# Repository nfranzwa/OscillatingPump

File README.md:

UCSD MAE 156 Capstone Project

Link to UCSD Capstone Project Overview https://sites.google.com/eng.ucsd.edu/mae156b-2025winter-team06

The provided code was developed using Arduino IDE and the Platform.io extension on VS Code.
While it is possible to flash/deploy our software to an ESP32 through other means, we heavily recommend the two for ease of installing dependencies and following subsequent instructions.

# Setup
In order to flash the GPIO ESP or Web ESP, first make a local copy of the most recent version of this repository by clicking `<Code>` and either:

 - Copying and running the command in terminal (requires github cli installation or git)
 - Opening through Github Desktop (requires installing the Github Desktop app)
 - Downloading and extracting the code from a .zip file

The next steps assume you have a local copy of the provided code.

# Installing Libraries

## GPIO ESP

Click the Platform IO icon on the left edge of VS Code, then navigate to `Quick Access > PIO Home > Projects & Configuration`.

Select `Add Existing`.

Navigate to the directory `drive/path/to/repository/OscillatingPump/ESP32_CTRL` and select `Open "ESP32_CTRL`.

Shortly, Platform IO should be setting up the project according to the `platform.ini` file in the selected folder, most importantly installing libraries that are used in the project.

## Web ESP

Open the Arduino sketch named `webesp.ino` located in `/WebappCode/webesp/webesp/`.

Navigate to the library manager.

Search for and install the following libraries:
 - Arduino_JSON by Arduino
 - Async TCP by ESP32Async
 - ESP Async WebServer by ESP32ASync
 - EspSoftwareSerial by Dirk Kaar, Peter Lerup

In the top menu, Navigate to `Sketch > Include Library`, and include the following:
 - WiFi
 - LittleFS

The next step is to install ESP32 LittleFS uploader to the Arduino IDE.

Go to [[https://github.com/earlephilhower/arduino-littlefs-upload/releases]] and download the latest version of `arduino-littlefs-upload-x.x.x.vsix`.

Windows: 
1. In File Explorer, navigate to `C:\Users\<username>\.arduinoIDE\`
2. Create a folder called `plugins` if it doesn't already exist.
3. Move the downloaded `.vsix` file into this folder.

Mac OS: 
1. In Finder, navigate to `~/.arduinoIDE`
2. Create a new folder called `plugins`
3. Move the downloaded `.vsix` file into this folder.

Restart the Arduino IDE, and make sure the plug-in was successfully installed by opening the command palette with `Ctrl/Cmd + Shift + P` and ensuring `Upload LittleFS to Pico/ESP8266/ESP32` is an available command.

# Uploading/Deploying code to the ESP32's

With the environments and libraries set up, one can compile and deploy the code through the following procedures.

## GPIO ESP

On the bottom bar, ensure that the Platform IO project is ESP32_CTRL and you are deploying to the right COM port (leave as `Auto` unless multiple ESP's are connected to same computer).

The code will be compiled and deployed to the ESP32 when pressing the `→` button.
 - one can also compile the code without deploying by pressing the `✓` button.

A new terminal should open within VS Code, displaying compile messages. When the terminal says `Connecting...`
Press and hold the `Boot` button on the ESP until the terminal shows that code is being written to the ESP32.

## Web ESP
First, Go to `Sketch > Show Sketch Folder` and ensure that the `data/` folder from our repository is there. This contains files that are to be uploaded to the ESP32 filesystem.

Open the command palette and run `Upload LittleFS to Pico/ESP8266/ESP32`.

After getting a `Completed upload` message, compile and deploy the sketch to the ESP32 by pressing the `→` button.
 - one can also compile the code without deploying by pressing the `✓` button.

When the terminal says `Connecting...`
Press and hold the `Boot` button on the ESP until the terminal shows that code is being written to the ESP32.

# Troubleshooting code
If the ESP's are consistently not behaving as expected, we provide debugging statements through Serial Monitors, which can be accessed through the Command Palette of both VS Code and Arduino IDE.

Issues to check may include whether an ESP is:
 - constantly restarting (stuck in a boot loop)
 - unable to communicate through serial with the other ESP
 - some particular features are not behaving as expected
 - error codes being thrown by an ESP

The GPIO ESP has an ongoing task that reads the Serial port between the computer and ESP, providing the user with the following inputs and features:

| User Input      | Feature                                                            |
| --------------- | ------------------------------------------------------------------ |
| `debug`         | toggles debugging statements for Serial communication between ESPs |
| `cal debug`     | toggles debugging statements for during calibration                |
| `wave debug`    | toggles debugging statements for wave generation                   |
| `show pm`       | prints out the current pressure map vector                         |
| `m:#.## M:#.##` | manually overwrite the target min and max pressure                 |
| `c:#`           | manually overwrite the calibration state                           |

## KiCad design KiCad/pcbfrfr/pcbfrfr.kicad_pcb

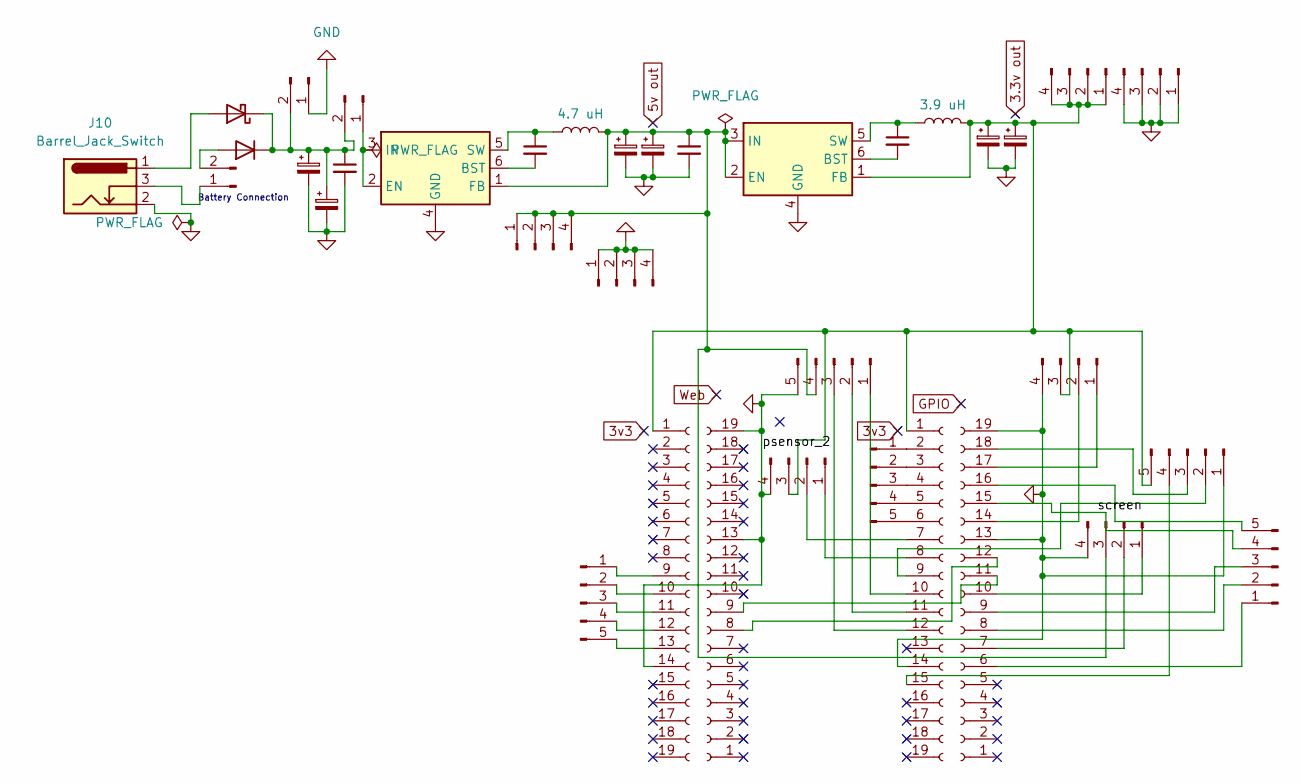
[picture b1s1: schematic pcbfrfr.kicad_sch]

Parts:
C1: 10 uF; CP_Radial_D4.0mm_P1.50mm
C2, C8: 100 nF; C_0402_1005Metric
C3, C4, C9, C10: 22 uF; C_0805_2012Metric
C5: 1000 uF; CP_Radial_D10.0mm_P5.00mm
C6, C7: 0.1 uF; C_0402_1005Metric
D2: US2AA; D_SMA
D3: SS24; D_SMA
J1, J11, J16, J17, J18: Conn_01x05_Pin; PinHeader_1x05_P2.54mm_Vertical
J2: battery; PinHeader_1x02_P2.54mm_Vertical
J3, J4, J5, J7: Conn_01x19_Socket; PinHeader_1x19_P2.54mm_Vertical
J6, J8, J9, J12, J13, J14, J15: Conn_01x04_Pin; PinHeader_1x04_P2.54mm_Vertical
J10: Barrel_Jack_Switch; BarrelJack_CLIFF_FC681465S_SMT_Horizontal
J21: mtr; PinHeader_1x02_P2.54mm_Vertical
J22: estop; PinHeader_1x02_P2.54mm_Vertical
L1: 4.7 uH; L_Changjiang_FXL0530
L3: 3.9 uH; L_Changjiang_FXL0530
U1: AP63203WU; TSOT-23-6
U2: AP63205WU; TSOT-23-6

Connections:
/screen: J5.15, J17.4
GND: C1.2, C3.2, C4.2, C5.2, C6.2, C7.2, C9.2, C10.2, J1.5, J3.14, J4.14, J5.13, J5.19, J6.4, J7.13, J7.19, J8.4, J9.4, J10.2, J11.1, J13.1, J13.2, J13.3, J13.4, J15.1, J15.2, J15.3, J15.4, J21.1, U1.4 (GND), U2.4 (GND)
unnamed: D2.2 (A), J2.2
unnamed: C1.1, C5.1, C6.1, D2.1 (K), D3.1 (K), J21.2, J22.2
unnamed: D3.2 (A), J10.1
unnamed: J1.1, J4.10
unnamed: J1.2, J4.11
unnamed: J1.3, J4.12
unnamed: C3.1, C4.1, C7.1, J1.4, J9.3, J12.1, J12.2, J12.3, J12.4, L1.2, U1.2 (EN), U1.3 (IN), U2.1 (FB)
unnamed: J2.1, J10.3
unnamed: J4.7, J8.2
unnamed: J4.8, J8.1
unnamed: J5.7, J9.2
unnamed: J5.10, J9.1
unnamed: J5.11, J7.9
unnamed: J5.12, J7.8
unnamed: J5.14, J6.2
unnamed: J5.17, J6.1
unnamed: J4.9, J11.2
unnamed: J5.18, J11.3
unnamed: J4.15, J11.4
unnamed: C9.1, C10.1, J3.1, J4.1, J6.3, J8.3, J11.5, J14.1, J14.2, J14.3, J14.4, L3.2, U1.1 (FB)
unnamed: J4.2, J16.1
unnamed: J4.3, J16.2
unnamed: J4.4, J16.3
unnamed: J4.5, J16.4
unnamed: J4.6, J16.5
unnamed: J5.6, J17.1
unnamed: J5.8, J17.2
unnamed: J5.9, J17.3
unnamed: J5.16, J17.5
unnamed: J3.9, J18.1
unnamed: J3.10, J18.2
unnamed: J3.11, J18.3
unnamed: J3.12, J18.4
unnamed: J3.13, J18.5
unnamed: J22.1, U2.2 (EN), U2.3 (IN)
unnamed: C8.2, U1.6 (BST)
unnamed: C8.1, L3.1, U1.5 (SW)
unnamed: C2.2, U2.6 (BST)
unnamed: C2.1, L1.1, U2.5 (SW)

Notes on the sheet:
Battery Connection

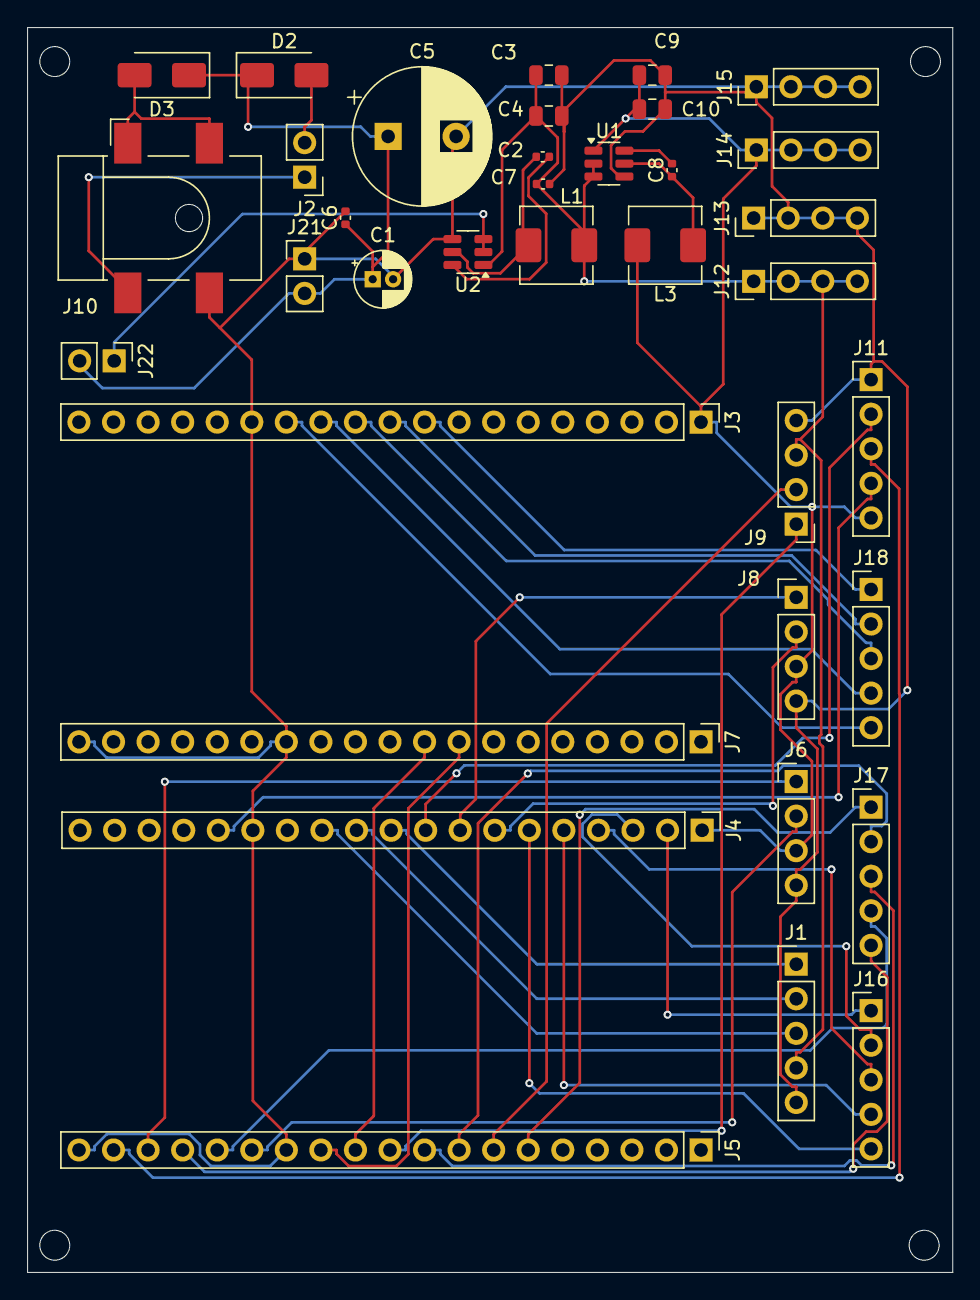
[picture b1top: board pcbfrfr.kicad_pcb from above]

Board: 2 copper layers, 68.0 x 91.5 mm, 36 parts (0 on the bottom side), 41 nets.

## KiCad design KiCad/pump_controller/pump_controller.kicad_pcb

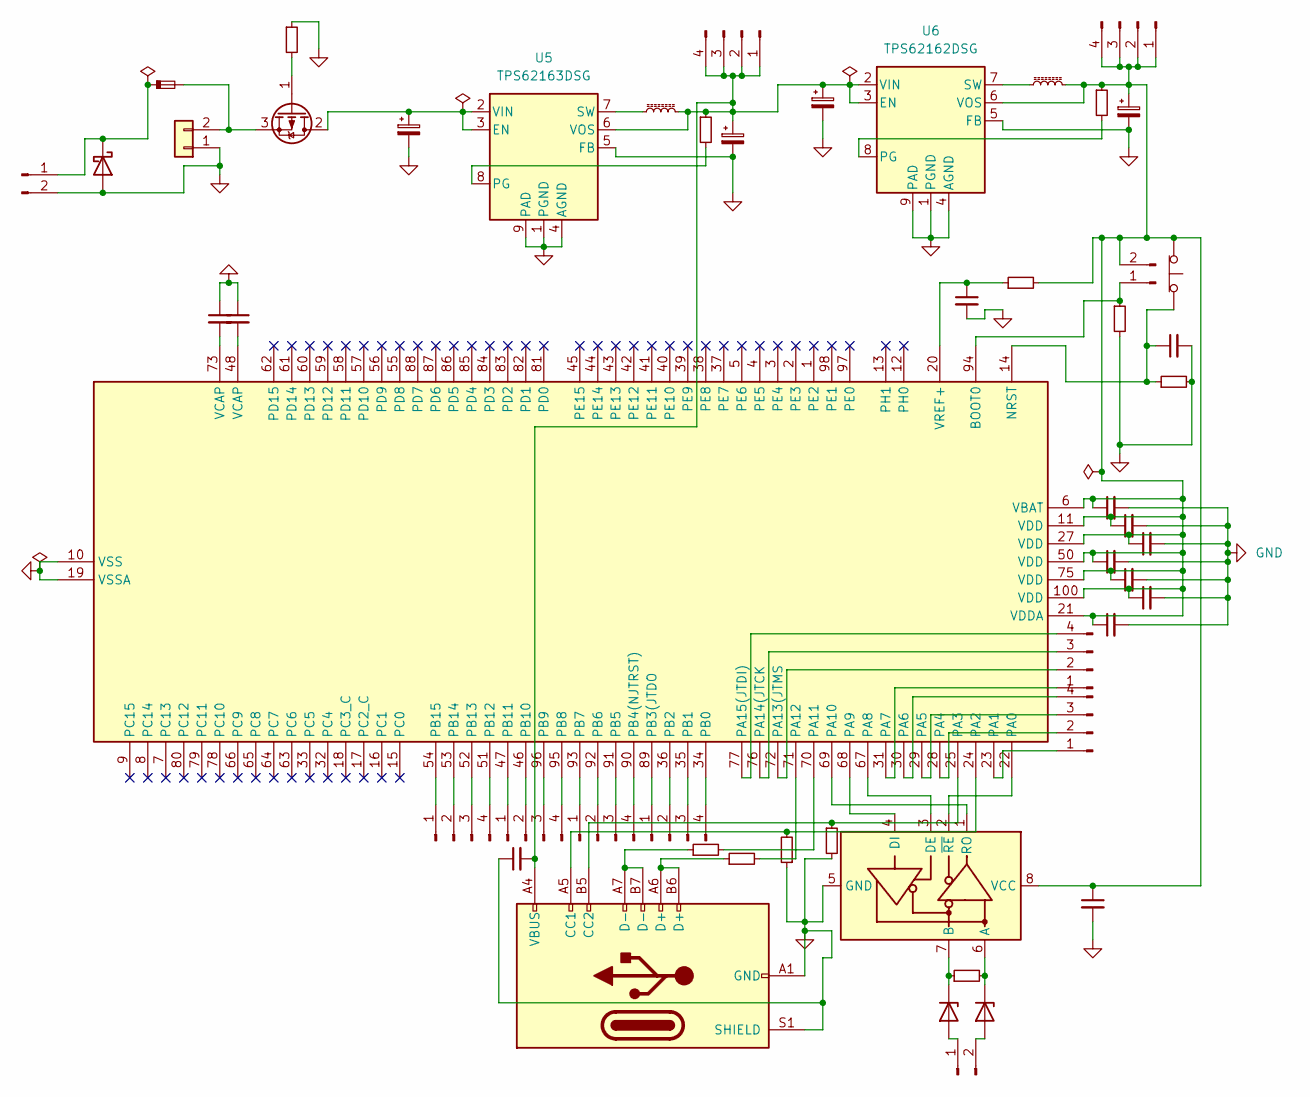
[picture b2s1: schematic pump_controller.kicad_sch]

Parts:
C2, C3: 2.2 uF; C_0402_1005Metric
C6, C10, C13, C14, C15, C16, C18, C19, C20, C21, C22: 0.1 uF; C_0402_1005Metric
C23, C25: 10 uF; CP_Elec_10x10.5
C24, C26: 22 uF; C_0805_2012Metric
D3, D5: PTVS7V5Z1USK; Nexperia_DSN1608-2_1.6x0.8mm
D6: 1N5819; D_DO-41_SOD81_P10.16mm_Horizontal
F2: 5A; Fuse_0805_2012Metric
J1, J2, J10, J12, J13, J17, J22, J23: Conn_01x04_Pin; PinHeader_1x04_P2.54mm_Vertical
J15: USB_C_Receptacle_USB2.0_14P; USB_C_Receptacle_HRO_TYPE-C-31-M-12
J21, J25, J30: Conn_01x02_Pin; PinHeader_1x02_P2.54mm_Vertical
J28: Conn_01x02; TerminalBlock_Phoenix_MKDS-1,5-2_1x02_P5.00mm_Horizontal
L3, L4: 2.2 uH; L_0805_2012Metric
Q2: IRF9540N; TO-220-3_Vertical
R2, R3, R7: 22; R_0402_1005Metric
R4, R5: 5100; R_0402_1005Metric
R6: 120; R_0402_1005Metric
R8, R9, R10: 10k; R_0402_1005Metric
R11, R12: 100k; R_0402_1005Metric
SW1: SW_Push_Open; SW_SPST_TL3342
U2: STM32H723VGTx; LQFP-100_14x14mm_P0.5mm
U4: MAX3075E; SOIC-8_3.9x4.9mm_P1.27mm
U5: TPS62163DSG; WSON-8-1EP_2x2mm_P0.5mm_EP0.9x1.6mm_ThermalVias
U6: TPS62162DSG; WSON-8-1EP_2x2mm_P0.5mm_EP0.9x1.6mm_ThermalVias

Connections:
GND: C2.1, C3.1, C6.1, C10.2, C13.2, C14.2, C15.2, C16.2, C18.2, C19.2, C20.2, C21.2, C22.2, C23.2, C24.2, C25.2, C26.2, D6.2 (A), J15.A1 (GND), J15.A12 (GND), J15.B1 (GND), J15.B12 (GND), J15.S1 (SHIELD), J28.1, J30.2, R4.1, R5.2, R8.2, R9.2, R10.1, U2.10 (VSS), U2.19 (VSSA), U2.26 (VSS), U2.49 (VSS), U2.74 (VSS), U2.99 (VSS), U4.5 (GND), U5.1 (PGND), U5.4 (AGND), U5.5 (FB), U5.9 (PAD), U6.1 (PGND), U6.4 (AGND), U6.5 (FB), U6.9 (PAD)
unnamed: C2.2, U2.73 (VCAP)
unnamed: C3.2, U2.48 (VCAP)
unnamed: D3.2 (A), J21.1
unnamed: D3.1 (K), R6.1, U4.7 (B)
unnamed: D5.2 (A), J21.2
unnamed: D5.1 (K), R6.2, U4.6 (A)
unnamed: D6.1 (K), F2.1, J30.1
unnamed: C6.2, C24.1, C25.1, J1.1, J1.2, J1.3, J1.4, J15.A4 (VBUS), J15.A9 (VBUS), J15.B4 (VBUS), J15.B9 (VBUS), L3.2, R11.1, U5.6 (VOS), U6.2 (VIN), U6.3 (EN)
unnamed: C13.1, C14.1, C15.1, C16.1, C18.1, C19.1, C20.1, C21.1, C26.1, J2.1, J2.2, J2.3, J2.4, J25.2, L4.2, R7.2, R12.1, SW1.1 (A), U2.6 (VBAT), U2.11 (VDD), U2.21 (VDDA), U2.27 (VDD), U2.50 (VDD), U2.75 (VDD), U2.100 (VDD), U4.8 (VCC), U6.6 (VOS)
unnamed: J10.1, U2.54 (PB15)
unnamed: J10.2, U2.53 (PB14)
unnamed: J10.3, U2.52 (PB13)
unnamed: J10.4, U2.51 (PB12)
unnamed: J12.1, U2.47 (PB11)
unnamed: J12.2, U2.46 (PB10)
unnamed: J12.3, U2.96 (PB9)
unnamed: J12.4, U2.95 (PB8)
unnamed: J13.1, U2.93 (PB7)
unnamed: J13.2, U2.92 (PB6)
unnamed: J13.3, U2.91 (PB5)
unnamed: J13.4, U2.90 (PB4(NJTRST))
unnamed: J15.A5 (CC1), R4.2, U2.24 (PA2)
unnamed: J15.B5 (CC2), R5.1, U2.25 (PA3)
unnamed: J15.A6 (D+), J15.B6 (D+), R3.1
unnamed: J15.A7 (D-), J15.B7 (D-), R2.1
unnamed: J17.1, U2.89 (PB3(JTDO)
unnamed: J17.2, U2.36 (PB2)
unnamed: J17.3, U2.35 (PB1)
unnamed: J17.4, U2.34 (PB0)
unnamed: J22.1, U2.31 (PA7)
unnamed: J22.2, U2.72 (PA13(JTMS)
unnamed: J22.3, U2.76 (PA14(JTCK)
unnamed: J22.4, U2.77 (PA15(JTDI))
unnamed: J23.1, U2.23 (PA1)
unnamed: J23.2, U2.28 (PA4)
unnamed: J23.3, U2.29 (PA5)
unnamed: J23.4, U2.30 (PA6)
unnamed: J25.1, R8.1, U2.94 (BOOT0)
unnamed: F2.2, J28.2, Q2.3 (S)
unnamed: C23.1, Q2.2 (D), U5.2 (VIN), U5.3 (EN)
unnamed: Q2.1 (G), R10.2
unnamed: C22.1, R9.1, SW1.2 (B), U2.14 (NRST)
unnamed: U2.22 (PA0), U4.2 (~RE)
unnamed: U2.67 (PA8), U4.3 (DE)
unnamed: U2.68 (PA9), U4.4 (DI)
unnamed: U2.69 (PA10), U4.1 (RO)
unnamed: R2.2, U2.70 (PA11)
unnamed: R3.2, U2.71 (PA12)
unnamed: C10.1, R7.1, U2.20 (VREF+)
unnamed: R11.2, U5.8 (PG)
unnamed: L3.1, U5.7 (SW)
unnamed: R12.2, U6.8 (PG)
unnamed: L4.1, U6.7 (SW)

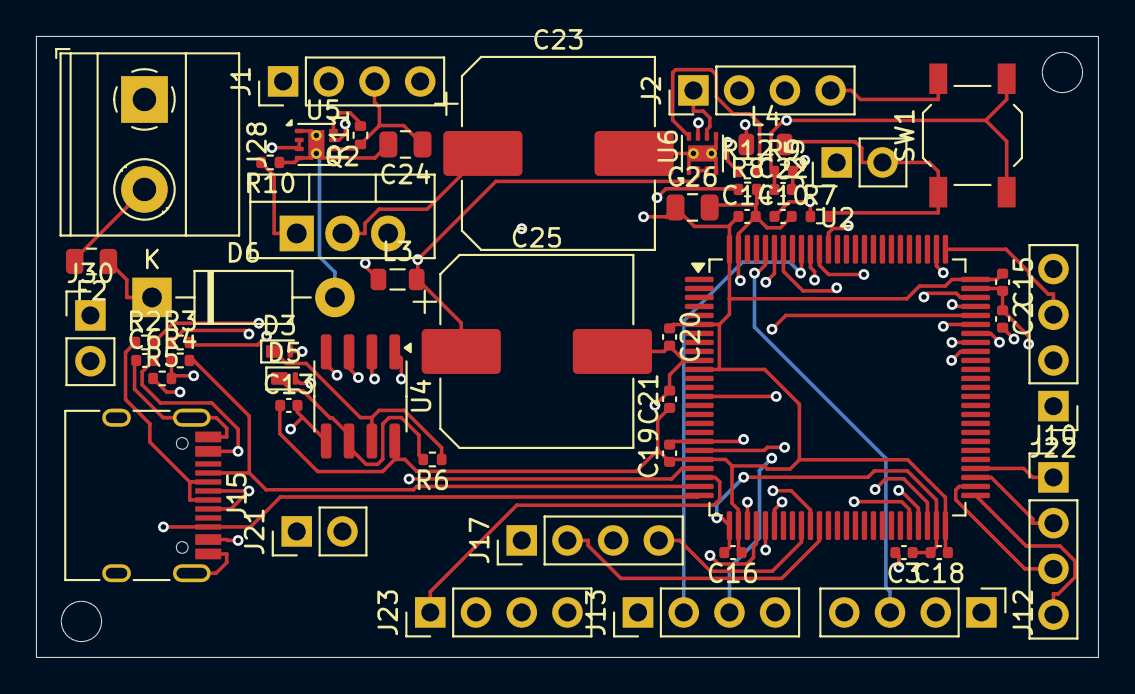
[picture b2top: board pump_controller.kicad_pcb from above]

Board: 4 copper layers, 59.0 x 34.5 mm, 53 parts (0 on the bottom side), 54 nets.

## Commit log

2025-01-10 KiCad
2025-01-10 Pictures
2025-01-10 media folder created
2025-01-10 reupload
2025-01-10 test code
2025-01-11 gui/arduino
2025-01-13 Create WebAppCode
2025-01-13 Agasthya Code for website
2025-01-13 Agasthya renames
2025-01-13 Agasthya requirements.txt
2025-01-21 Agasthya new webapp code
2025-01-23 Create temp_ignore
2025-01-23 Webapp
2025-01-29 matlab
2025-01-30 Agasthya webapp commits
2025-01-30 Agasthya update
2025-02-02 Agasthya edits
2025-02-02 agasthya
2025-02-03 agasthya bluh
2025-02-04 Agasthya commits
2025-02-05 reorganize agasthya
2025-02-05 testcode
2025-02-06 Basic open-loop implementation
    Add adjustable target waveform with PWM,
    interface for browsing and alternating values,
    implemented safeguard against SAVING invalid values for waveform properties.
    Framework for pressure sensor and filter; needs to be tested
2025-02-12 Agasthya minor changes
2025-02-13 everything works rn apart from download
2025-02-13 FINALLY WORKS
2025-02-13 reorganizing
2025-02-13 smol changes
2025-02-18 Physical UI V1
    LCD display of sensor data, target value, and interaction with rotary encoder to change between view modes (edit, view, temp).
    TODO: task handlers with FreeRTOS to run LCD on separate core, as it currently interrupts the rotary encoder detecting correct input
2025-02-18 pcbround2
2025-02-19 round2
2025-02-19 Agasthya python web scraper
2025-02-19 newcontrol
2025-02-19 Agasthya client side
2025-02-20 newpcb
2025-02-20 UI fixed, Free RTOS implemented
    Updated UI to run encoder, sensor, and wave generator on separate code from LCD. UI modified to change between view modes (ASDR, soon other modes) by short clicks, and edit parameters by holding down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
2025-02-20 smallplot
2025-02-21 Motor + Physical UI Consolidated
    🎉 Motor controlled by ASDR and adjustable via physical UI
2025-02-21 safety for asdr params
2025-02-21 gitignore has its uses
2025-02-25 phys UI + barebones for I2C sensor
2025-02-25 Agasthya new UI
2025-02-25 ported over ESP communication code
    Still needs to change variables to be the ones we want to change
2025-02-26 debugging
2025-02-26 brian stfu
2025-02-26 Agasthya i couldnt tweak the motor sorry
2025-02-26 Pressure mapping and rudimentary calibration code
    Still needs a feature to allow user to trigger when to start the calibration
2025-02-26 i fixed the world
2025-02-27 Calibration Modes and communication w/ web esp
2025-02-27 curchanges Agasthya
2025-03-03 updatedpcb
2025-03-06 Agasthya gpiosep
2025-03-06 Calibration and dummy sensor code, serial comm NEEDS fixs
    core 0 is being hogged by the talk2web task, as it is taking too long to listen. additionally need to optimize the priorities and memory given to each task. Start breaking code into smaller functions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
2025-03-06 debug serial comm
    cant seem to read properly
2025-03-06 added barebones serial comm test between esp + maybe arduino
2025-03-06 Test demonstrates ESP-ESP Serial Comm on PlatformIO
2025-03-06 Proof of communication protocol through serial between two ESP from Platformio
2025-03-06 minor update to serial test
2025-03-07 15 big monkeys
2025-03-07 Brian loves kids
2025-03-07 brian was here
2025-03-07 Agasthya gpiomerge
2025-03-07 Updated GPIO for new I2C sensor
    Stable release
2025-03-07 greying out slider
2025-03-07 dummy serial code updated
    now can input values and toggle to read current value
2025-03-07 edits, everything works but breaks without lcd or motor connected
2025-03-07 agasthya refine gpiocode
2025-03-07 Change baud rate
2025-03-07 minor change for test serial
2025-03-08 i dont have time for the name
    more thorough code for error feedback and status LED
2025-03-08 pressure map update
    added initial values for testing waveform and pressure map without calibrating
2025-03-08 3.8.2025
    serial communication is not running
2025-03-09 finally have communication
    code still fighting on shared values,
    calibration needs to be ironed out
2025-03-09 added some serial testing
    user can input "mp:%f" for debugging mapPos(float pressure) to test the pressure map (you receive an integer PWM position for desired pressure)
    user can input "c:%d" for manually changing calibration state
2025-03-09 big daddy
2025-03-09 🎉 Monotonic pressure mapping + Calibration code
    Waveform also works, but logic for setting the PWM_last_min during loops must be correct
2025-03-09 feedback loop change
2025-03-09 Script changes agasthya
2025-03-11 publish error code to Web ESP
    also a little bit of experimenting for changing waveform shape
2025-03-11 Agasthya further changes
2025-03-11 idle position for when calibration state=0
2025-03-12 updated pins for PCB
2025-03-12 I think I am being converted to Catholicism
2025-03-15 Agasthya - Final changes on home pc. Further verification on chromebook
2025-03-15 Cleanup
